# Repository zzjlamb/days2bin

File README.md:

# Days2Bin

An indicator to show number of days until different kerbside
bins/trash/recycling etc are due to be collected.

## Hardware

Raspberry Pi Pico W, DS3231 RTC and
Core Electronics GlowBit (based on WS2812 addressable LEDs).
 
The device is powered by 3 x AAA batteries switched by a pair of logic level MOSFETs
triggered by grounding via a momentary pushbutton, then kept alive
by one of the Pico W GPIO's until the Pico logic shuts it down.

A separate pair of AAA batteries powers the DS3231 RTC. I try to avoid button batteries for child safety reasons. These should last much longer than the main batteries due to the very low current drain of the DS3231, and having them saves having to re-enter the time.

The settings are stored in a dedicated page of flash, which is reserved by a custom loader script.

Settings are entered by holding the pushbutton down until a Wifi symbol is displayed, and joining the Days2Bin wifi access point. Apple devices should then display the settings page via captive portal. Other devices can display the page by browsing to http://192.168.4.1 after joining the access point.

Up to three bins can be configured: general waste, recyling, and green waste. The device scrolls the number of days to each type in red, yellow and green colours respectively, then powers off, unless the button is held on, in which case Settings mode is entered.

On first use, or if the clock battery has failed, users are prompted to join the access point.

Time out for the access point is 2 minutes.

This project was coded entirely in C using the Pico SDK. I originally tried to code it in MicroPython, however the startup time was several seconds, whereas the C version is virtually instantaneous.

2024 by John Lamb
Licenced under MIT Licence

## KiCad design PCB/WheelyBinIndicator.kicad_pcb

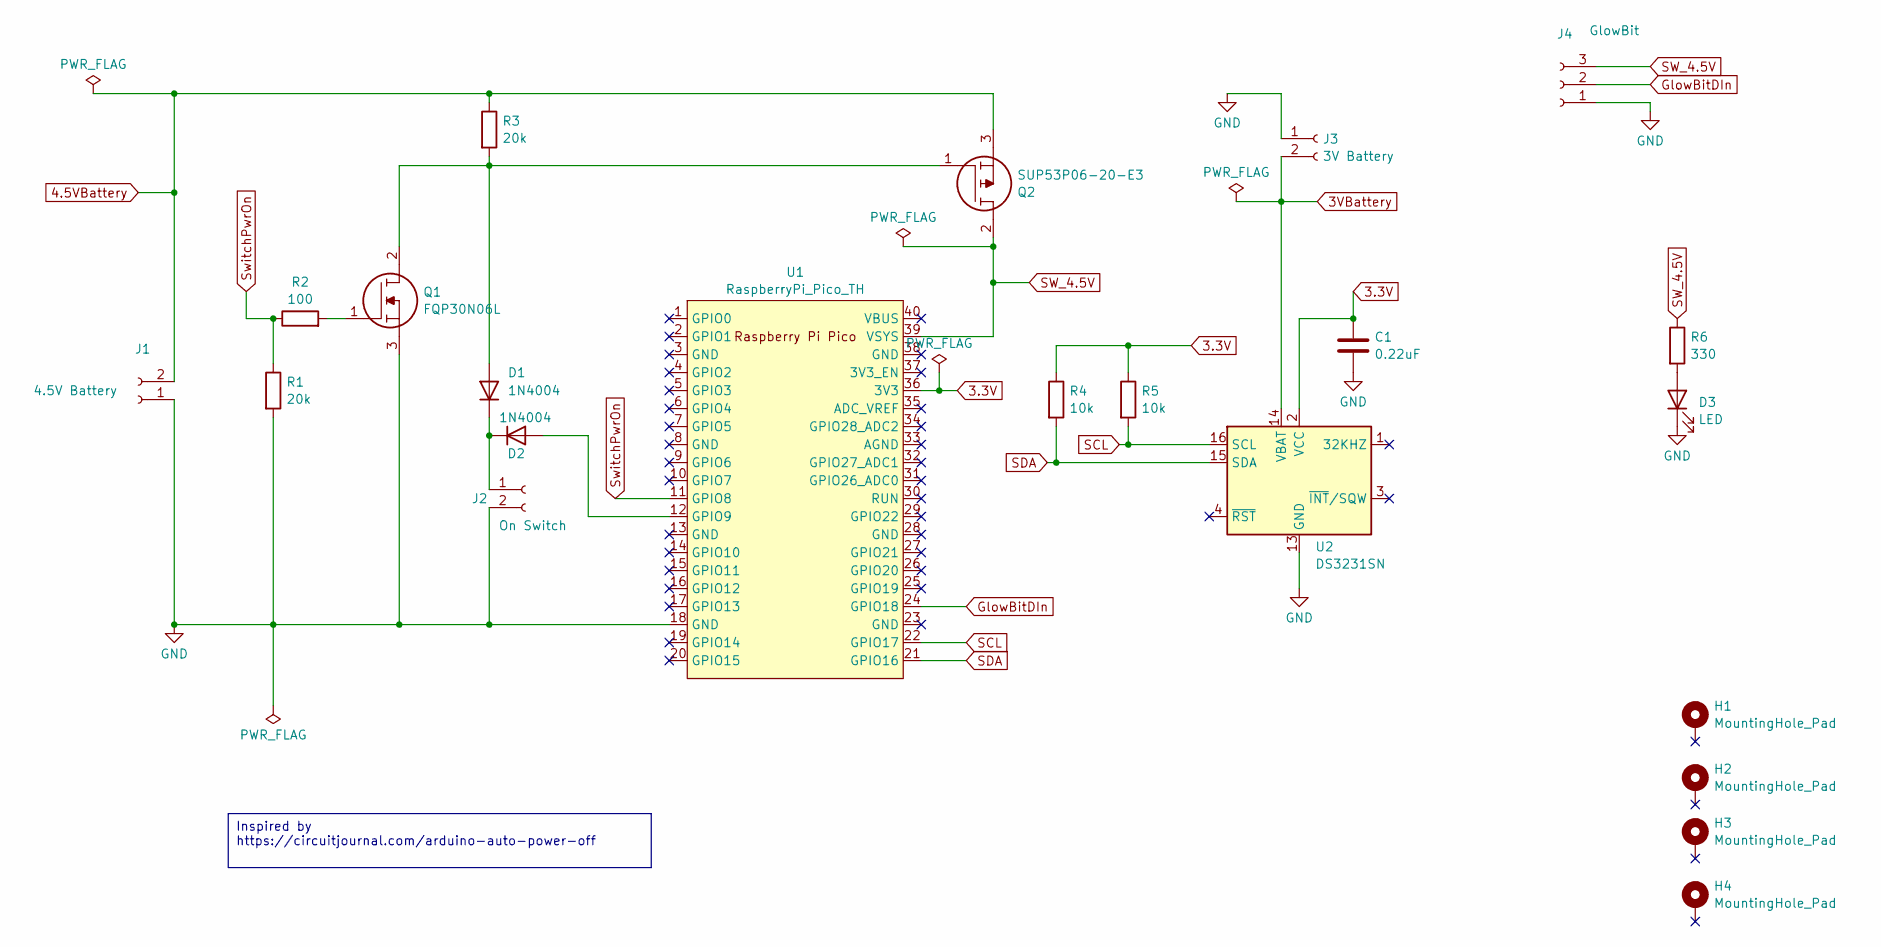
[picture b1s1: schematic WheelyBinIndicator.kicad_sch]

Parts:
C1: 0.22uF; C_Disc_D4.7mm_W2.5mm_P5.00mm
D1, D2: 1N4004; D_A-405_P7.62mm_Horizontal
D3: LED; LED_D5.0mm
H1, H2, H3, H4: MountingHole_Pad; MountingHole_3.2mm_M3_Pad
J1: 4.5V Battery; JST_XH_B2B-XH-A_1x02_P2.50mm_Vertical
J2: On Switch; JST_XH_S2B-XH-A-1_1x02_P2.50mm_Horizontal
J3: 3V Battery; JST_XH_B2B-XH-A_1x02_P2.50mm_Vertical
J4: GlowBit; JST_XH_S3B-XH-A-1_1x03_P2.50mm_Horizontal
Q1: FQP30N06L; TO-220-3_Vertical; Manufacturer_Part_Number FQP30N06L; Mouser Part Number 512-FQP30N06L
Q2: SUP53P06-20-E3; TO-220-3_Vertical; Manufacturer_Part_Number SUP53P06-20-E3; Mouser Part Number 781-SUP53P06-20-E3
R1, R3: 20k; R_Axial_DIN0207_L6.3mm_D2.5mm_P7.62mm_Horizontal
R2: 100; R_Axial_DIN0207_L6.3mm_D2.5mm_P7.62mm_Horizontal
R4, R5: 10k; R_Axial_DIN0207_L6.3mm_D2.5mm_P7.62mm_Horizontal
R6: 330; R_Axial_DIN0207_L6.3mm_D2.5mm_P7.62mm_Horizontal
U1: RaspberryPi_Pico_TH; RPi_Pico_TH
U2: DS3231SN; SOIC-16W_7.5x10.3mm_P1.27mm

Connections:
3.3V: C1.1, R4.1, R5.1, U1.36 (3V3), U2.2 (VCC)
3VBattery: J3.2, U2.14 (VBAT)
4.5VBattery: J1.2, Q2.3, R3.1
GND: C1.2, D3.1 (K), J1.1, J2.2, J3.1, J4.1, Q1.3, R1.2, U1.18 (GND), U2.5 (GND), U2.6 (GND), U2.7 (GND), U2.8 (GND), U2.9 (GND), U2.10 (GND), U2.11 (GND), U2.12 (GND), U2.13 (GND)
GlowBitDIn: J4.2, U1.24 (GPIO18)
unnamed: D1.2 (A), Q1.2, Q2.1, R3.2
unnamed: D1.1 (K), D2.1 (K), J2.1
unnamed: D2.2 (A), U1.12 (GPIO9)
unnamed: D3.2 (A), R6.2
unnamed: Q1.1, R2.2
SCL: R5.2, U1.22 (GPIO17), U2.16 (SCL)
SDA: R4.2, U1.21 (GPIO16), U2.15 (SDA)
SW_4.5V: J4.3, Q2.2, R6.1, U1.39 (VSYS)
SwitchPwrOn: R1.1, R2.1, U1.11 (GPIO8)

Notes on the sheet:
Inspired by https://circuitjournal.com/arduino-auto-power-off

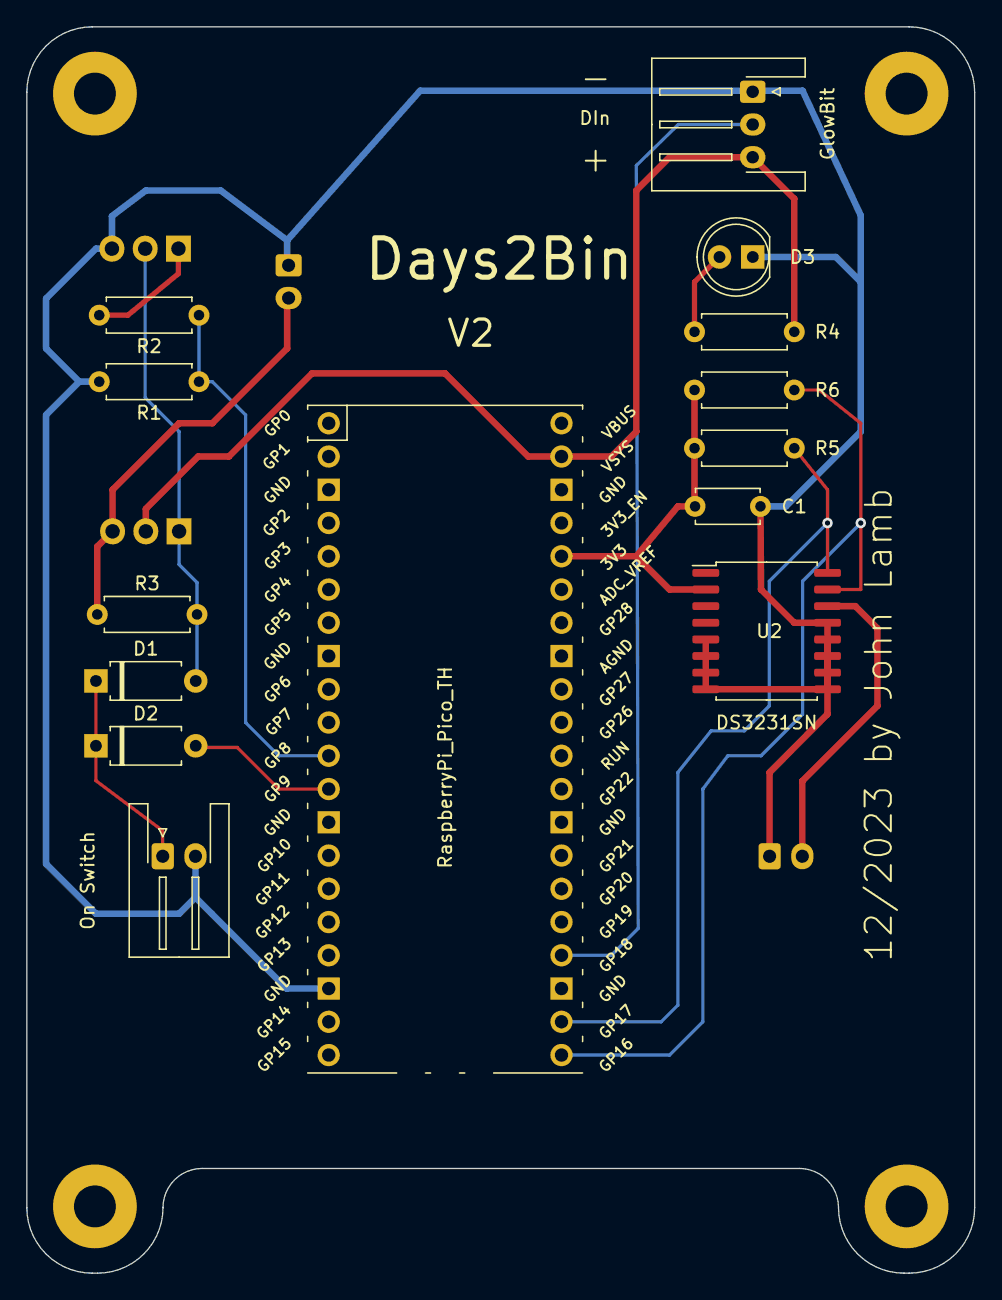
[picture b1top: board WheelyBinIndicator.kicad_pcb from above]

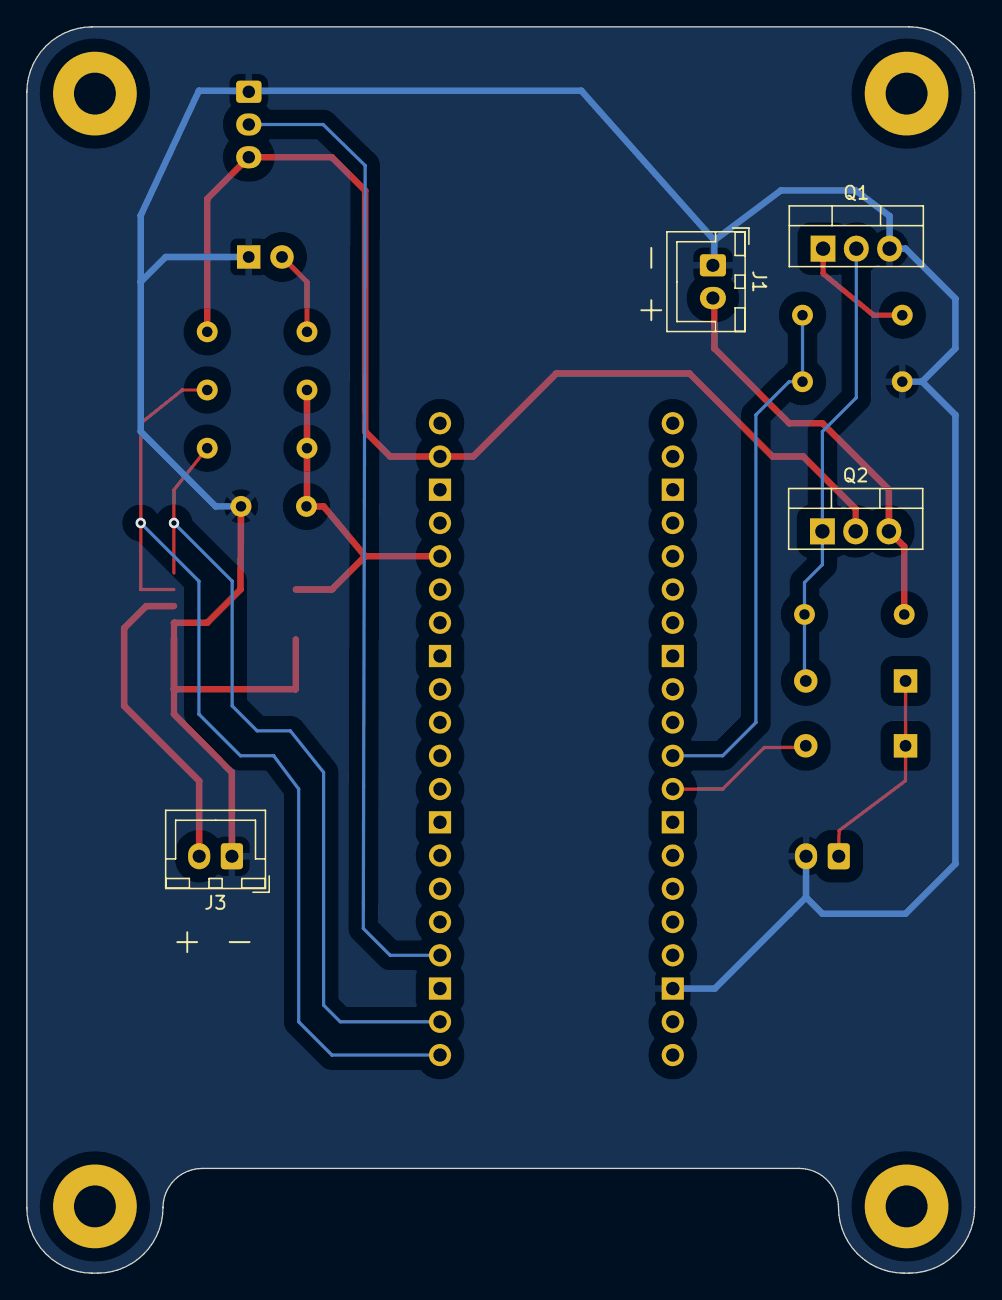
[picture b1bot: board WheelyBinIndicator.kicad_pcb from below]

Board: 2 copper layers, 72.4 x 95.2 mm, 22 parts (4 on the bottom side), 14 nets.

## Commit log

2024-01-01 new file: .vscode/c_cpp_properties.json new file: .vscode/extensions.json new file: .vscode/launch.json new file: .vscode/settings.json new file: CMakeLists.txt new file: glowbit.c new file: pico_sdk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
2024-01-01 First attempt at scrolling text
2024-01-01 Almost got the scrolling completed. Need to add arg for colour and also option to omit display flush at end.
2024-01-02 Still trying to Commit
2024-01-02 glowbit working, with I2c scan now too
2024-01-02 gitignore file added to root directory
2024-01-02 Added DS3231 code
2024-01-03 Successfully converted glowbit to cpp
2024-01-03 Working read of DS3231 and scroll result.
2024-01-04 Playing with flash partitioning
2024-01-08 Moved flashing code to own folder
2024-01-09 Got bindata to flash working
2024-01-10 Organised into subdirectories
2024-01-12 DS3231.cpp-> DS3231_new.cpp to change I2C pins
2024-01-12 Working on date maths
2024-01-14 working version without settings
2024-01-15 added access point code
2024-01-16 Added httpd
2024-01-20 access point workingbut not captive
2024-01-21 Added custom file handler for redirect
2024-01-22 working raw POST
2024-01-22 Untrack files in .gitignore
2024-01-22 pushed deletion of untracked files
2024-01-24 index.shtml updated
2024-01-24 Updated index.shtml
2024-02-07 Working on MacOS Host
2024-02-09 Flash write from cgi working
2024-02-09 Build folder removed from repo
2024-02-10 settingssaved.html added
2024-02-10 Working pus batt voltage/temp
2024-02-10 Added battery voltage
2024-02-11 .DS_Store removed from repo
2024-02-11 Pull up enabled for pwr on GPIO
2024-02-11 PCB added
2024-02-11 Schematic.pdf added
2024-02-11 README started
2024-02-11 Further work on the README
2024-02-11 Fixed error in colour definitions
2024-02-12 Added pictures to README
2024-02-12 3D Models added
